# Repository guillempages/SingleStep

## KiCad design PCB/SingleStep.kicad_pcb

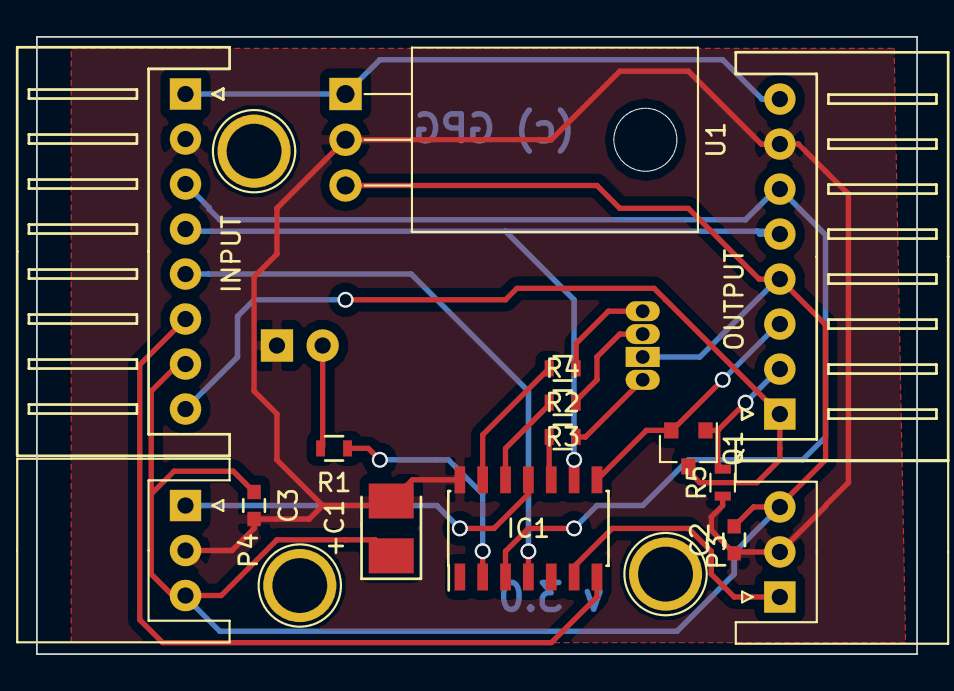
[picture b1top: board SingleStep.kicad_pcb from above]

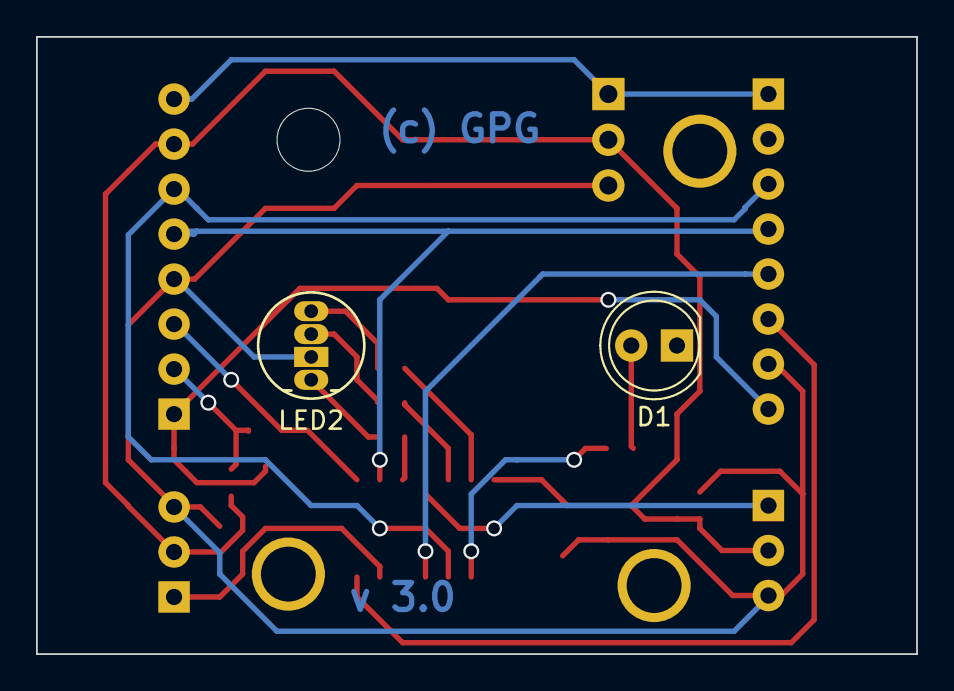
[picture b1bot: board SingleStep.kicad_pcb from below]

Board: 2 copper layers, 48.9 x 34.3 mm, 17 parts (2 on the bottom side), 20 nets.

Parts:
+C1: CP1; Tantalum_Case-B_EIA-3528-21_Reflow
C2, C3: C; C_0603
D1: LED; LED_D5.0mm
IC1: ATTINY24A-P; SOIC-14_3.9x8.7mm_Pitch1.27mm
LED2: BGAR; LED-RGB-5MM_Common_Cathode
P1: INPUT; JST_XH_S08B-XH-A_08x2.50mm_Angled
P2: OUTPUT; JST_XH_S08B-XH-A_08x2.50mm_Angled
P3: Light; JST_XH_S03B-XH-A_03x2.50mm_Angled
P4: IR; JST_XH_S03B-XH-A_03x2.50mm_Angled
Q1: MMBT3906; SOT-23
R1, R2, R3, R4, R5: R; R_0603
U1: LM7805; TO-220_Horizontal

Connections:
/CLK: IC1.9, P1.4, P2.5
/GND: +C1.2, C2.1, C3.2, D1.1, IC1.14, P1.2, P2.7, P3.2, P4.2, R5.1, U1.2
/MISO: IC1.8, P2.3, Q1.2
/MOSI: IC1.7, P1.6
/RST: IC1.4, P1.5
/SS: IC1.3, P1.3, P2.6
/Upstream MISO: P1.8, P2.1, Q1.3
/Vin: P1.1, P2.8, U1.1
unnamed: +C1.1, C2.2, C3.1, LED2.2, P1.7, P2.4, P3.3, P4.3, U1.3
unnamed: D1.2, R1.2
unnamed: IC1.2, R1.1
unnamed: IC1.6, P3.1
unnamed: IC1.10, R2.1
unnamed: IC1.11, P4.1
unnamed: IC1.12, R3.2
unnamed: IC1.13, R4.2
unnamed: LED2.1, R2.2
unnamed: LED2.3, R3.1
unnamed: LED2.4, R4.1
unnamed: P2.2, Q1.1, R5.2

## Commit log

2014-05-25 First working version.
    Pin4 input, Pin3 input with fade-out.
2014-05-28 Implement SPI communication
2014-05-28 Add Fade in/out, switch on/off functions
2014-05-29 Enable git in UI
2014-05-29 Add command definition file and execution.
2014-05-29 Move LED control functions to own file
2014-05-29 Misc cleanup
2014-05-29 Fix pinB4 read
    Was trying to read from the output register instead of the input one.
2014-05-29 Create definitions for device independent programming
2014-05-30 Add support for ATtiny 2313
2014-05-30 Add support for ATtiny24A
2014-06-01 Add ADC handling code
    Support light sensor and IR step sensor.
2014-06-12 Change the command definitions
    In preparation for a generic addressing model,
    change the definitions and add the new commands.
    Step sensor and light sensor got new incompatible values!
2014-06-12 Use generic commands for the sensors
    Add the possibility of reading more than one sensor.
    Also add first implementation of temperature reading (needs debugging)
2014-06-16 Define commands in HEX
2014-06-28 Add support for RGB LED (only ATtiny 24A)
2014-07-05 Add support for RGB led for attiny2331 and 85
    attiny85 has only compile support, but not enough pins for real RGB support.
2014-07-05 Fix bug in setLedState
    In case a led should be set to off, the address of that led was checked, and not the real status.
2014-07-05 Add implementation for eeprom read/write.
2014-07-06 Adapt pin outputs to PCB design
2014-07-06 Fix bug when setting RGB led on/off
    After setting white and off, the blue LED was shining, instead of switching off.
2014-07-06 Fix convenience commands
    Add support for RGB and new PCB pin design.
2014-09-21 Execute SPI commands only once.
2014-10-05 Refactor PWM functionality
    Add a new method to set LED brightness.
    Refactor PWM, and simplify the code.
2014-10-05 Add testMode
    Run a cycle on the LEDs until the first command is received.
    Useful to check that the flashing was successful.
2014-10-05 Increase white blinking frequency
    Make the white LED blink as fast as the green LED, so that boards with
    only White LEDS also show change.
2015-01-18 Increase blinking frequency even more
    Blink white and blue instead of green.
2015-01-18 Add constants for sensors
2015-01-18 Continuously read sensor values and average out
2015-05-15 Reset SPI when executing commands
    This will provide better synchronization when the Master Controller is reset.
2015-05-17 Add command to restart test mode
2017-03-07 Add initial PCB version
    The schematic has been updated to comply with the new KiCAD libraries.
2017-03-07 Add "Last step" jumper
    Also add version information to PCB
2017-03-07 Add kicad_pcb-bak to gitignore
2017-03-07 Change PCB to SMD
    Change most components to SMD components.
    Add LM7805 Voltage regulator.
    Add automatic last step detection.
2020-12-20 Allow setting brigtness values for all LEDs
    Make the Led Color constants available.
    Use LED_W for the white LED
